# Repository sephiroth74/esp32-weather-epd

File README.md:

> **Fork Notice**: This is a fork of [lmarzen/esp32-weather-epd](https://github.com/lmarzen/esp32-weather-epd) with additional features:
> - **Multiple location support**: Cycle through different locations on each refresh

# ESP32 E-Paper Weather Display

A low-power weather display using a wifi-enabled ESP32 microcontroller and a 7.5" E-Paper display. Weather data is fetched from the OpenWeatherMap API, and an onboard sensor provides indoor temperature and humidity.

## Features

- Ultra-low power consumption: ~14μA in sleep, ~83mA during refresh (~15s).

- Long battery life: 6-12 months on a 5000mAh battery with 30-minute update frequency.

- Customizable display: Supports multiple languages, units, time/date formats, AQI scales, personalization options, and much more.

- Easy recharging: USB-C charging with battery monitoring.

The hourly outlook graph (bottom right) shows a line indicating temperature and shaded bars indicating probability of precipitation (or optionally volume of precipitation).

Here are two (slightly outdated) examples utilizing various configuration options:

## Contents

- [ESP32 E-Paper Weather Display](#esp32-e-paper-weather-display)
  - [Features](#features)
  - [Contents](#contents)
  - [Required Components](#required-components)
    - [Panel Support](#panel-support)
    - [Enclosure Options](#enclosure-options)
    - [Solder-Free Component Selection (Optional)](#solder-free-component-selection-optional)
  - [Setup Guide](#setup-guide)
    - [Wiring](#wiring)
    - [Configuration, Compilation, and Upload](#configuration-compilation-and-upload)
    - [OpenWeatherMap API Key](#openweathermap-api-key)
  - [Error Messages and Troubleshooting](#error-messages-and-troubleshooting)
    - [Low Battery](#low-battery)
    - [WiFi Connection](#wifi-connection)
    - [API Error](#api-error)
    - [Time Server Error](#time-server-error)
  - [Licensing](#licensing)

## Required Components

  Some links below are affiliate links. Using them helps support the project at no extra cost to you—thanks for your support!

  | Component Type  | Component                                    | Notes                                                     | Link                                                                         |
  |-----------------|----------------------------------------------|-----------------------------------------------------------|------------------------------------------------------------------------------|
  | ESP32           | FireBeetle 2 ESP32-E                         | Features low-power design, USB-C, and battery management. | Available [here](https://www.dfrobot.com/product-2195.html?tracking=PfSxQ8). |
  | E-Paper Display | See [Panel Support](#panel-support).         | See [Panel Support](#panel-support).                      | See [Panel Support](#panel-support).                                         |
  | Adapter Board   | DESPI-C02                                    | Waveshare HATs (rev 2.2/2.3) are not recommended.         | Available [here](https://www.aliexpress.us/item/3256804446769469.html).      |
  | Sensor          | BME280                                       | Temperature, humidity, and pressure. 3.3V/5V compatible.  | Available from multiple vendors.                                             |
  | Battery         | 3.7V LiPo w/ JST-PH2.0 connector             | Any capacity (e.g., 5000mAh for 6+ months runtime)        | Available from multiple vendors.                                             |
  | Enclosure       | See [Enclosure Options](#enclosure-options). | See [Enclosure Options](#enclosure-options).              | See [Enclosure Options](#enclosure-options).                                 |

Other items needed:
- Wires ("Jumper Wires" if looking to minimize/avoid soldering).
- Solder Iron + Solder (unless following [Solder-Free Component Selection](#solder-free-component-selection-optional)).
- Linux, Windows, or MacOS computer (used to configure and install ESP32 firmware).
- Push Button (optional, if you want a reset button mounted on your enslosure, else you can use the on-board reset button).

### Panel Support

  Waveshare and Good Display make equivalent panels. Either variant will work.

  | Panel                                   | Resolution | Colors          | Notes                                                                                                                 |
  |-----------------------------------------|------------|-----------------|-----------------------------------------------------------------------------------------------------------------------|
  | Waveshare 7.5in e-paper (v2)            | 800x480px  | Black/White     | Available [here](https://www.waveshare.com/product/7.5inch-e-paper.htm). (recommended)                                |
  | Good Display 7.5in e-paper (GDEY075T7)  | 800x480px  | Black/White     | [Temporarily Unavailable](https://www.aliexpress.com/item/3256802683908868.html)? (wrong product listed?)             |
  | Waveshare 7.5in e-Paper (B)             | 800x480px  | Red/Black/White | Available [here](https://www.waveshare.com/product/7.5inch-e-paper-b.htm).                                            |
  | Good Display 7.5in e-paper (GDEY075Z08) | 800x480px  | Red/Black/White | Available [here](https://www.aliexpress.com/item/3256803540460035.html).                                              |
  | Waveshare 7.3in ACeP e-Paper (F)        | 800x480px  | 7-Color         | Available [here](https://www.waveshare.com/product/displays/e-paper/epaper-1/7.3inch-e-paper-f.htm).                  |
  | Good Display 7.3in e-paper (GDEY073D46) | 800x480px  | 7-Color         | Available [here](https://www.aliexpress.com/item/3256805485098421.html).                                              |
  | Waveshare 7.5in e-paper (v1)            | 640x384px  | Black/White     | Limited support. Some information not displayed, see [image](showcase/demo-waveshare75-version1.jpg).                 |
  | Good Display 7.5in e-paper (GDEW075T8)  | 640x384px  | Black/White     | Limited support. Some information not displayed, see [image](showcase/demo-waveshare75-version1.jpg).                 |

  This software has limited support for accent colors. E-paper panels with additional colors tend to have longer refresh times, which will reduce battery life.

### Enclosure Options

You'll want a nice way to show off your project. Here are a few popular choices.

- DIY Wooden
  - I made a small stand by hollowing out a piece of wood from the bottom. On the back, I used a short USB extension cable so that I can charge the battery without needing to remove the components from the stand. I also wired a small reset button to refresh the display manually. Additionally, I 3d printed a cover for the bottom, which is held on by magnets. The E-paper screen is very thin, so I used a thin piece of acrylic to support it.
  - Measurements:
    - depth = 63mm <br>
      height = 49mm <br>
      width = 170.2mm (= width of the screen) <br>
      screen angle = 80deg <br>
      screen is 15mm from the front
- 3D Printable
  - Here is a list of community designs.
  
    | Contributor                                                          | Link                                                                                                     |
    |----------------------------------------------------------------------|----------------------------------------------------------------------------------------------------------|
    | [Kingfisher](https://www.printables.com/@Kingfisher_32821)           | [Printables](https://www.printables.com/model/1139047-weather-station-e-ink-frame)                       |
    | [Francois Allard](https://www.printables.com/@FrAllard_1585397)      | [Printables](https://www.printables.com/model/791477-weather-station-using-a-esp32)                      |
    | [3D Nate](https://www.printables.com/@3DNate_451157)                 | [Printables](https://www.printables.com/model/661183-e-ink-weather-station-frame)                        |
    | [Sven F.](https://github.com/Spanholz)                               | [Printables](https://www.printables.com/model/657756-case-for-esp32-weather-station)                     |
    | [Layers Studio](https://www.printables.com/@LayersStudio)            | [Printables](https://www.printables.com/model/655768-esp32-e-paper-weather-display-stand)                |
    | [PJ Veltri](https://www.printables.com/@PJVeltri_1590999)            | [Printables](https://www.printables.com/model/692944-base-and-display-holder-for-esp-32-e-paper-weather) |
    | [TheMeanCanEHdian](https://www.printables.com/@TheMeanCanEH_1207348) | [Printables](https://www.printables.com/model/841458-weather-display-enclosure)                          |
    | [MPHarms](https://www.thingiverse.com/mpharms/designs)               | [Thingiverse](https://www.thingiverse.com/thing:6666148)                                                 |
    | [Plaste-Metz](https://www.printables.com/@PlasteMetz_576567)         | [Printables](https://www.printables.com/model/1160924-weather-station-case)                              |

  - If you want to share your own 3D printable designs, your contributions are highly encouraged and welcome!
- Picture Frame

### Solder-Free Component Selection (Optional)

This project can be completed without any soldering, if you choose your component selection carefully.
- Buy "Jumper Wires" to connect your components.
- Buy the [FireBeetle 2 ESP32-E w/ Headers](https://www.dfrobot.com/product-2231.html?tracking=PfSxQ8).
- Buy a BME280 with headers soldered from the factory.
- Buy a reset switch that is compatible with jumper wires.

## Setup Guide

### Wiring

The battery can be charged by plugging the FireBeetle ESP32 into the wall via the USB-C connector while the battery is plugged into the ESP32's JST connector.

  > **Warning**
  > The polarity of JST-PH2.0 connectors is not standardized! You may need to swap the order of the wires in the connector.

NOTE: Waveshare now ships revision 2.3 of their e-paper HAT (no longer rev 2.2 ). Rev 2.3 has an additional `PWR` pin (not depicted in the wiring diagrams below); connect this pin to 3.3V.

IMPORTANT: The DESPI-C02 adapter has one physical switch that MUST be set correctly for the display to work.

- RESE: Set switch to position 0.47.

IMPORTANT: The Waveshare E-Paper Driver HAT has two physical switches that MUST be set correctly for the display to work.

- Display Config: Set switch to position B.

- Interface Config: Set switch to position 0.

Cut the low power pad for even longer battery life.

- From <https://wiki.dfrobot.com/FireBeetle_Board_ESP32_E_SKU_DFR0654>

  > Low Power Pad: This pad is specially designed for low power consumption. It is connected by default. You can cut off the thin wire in the middle with a knife to disconnect it. After disconnection, the static power consumption can be reduced by 500 μA. The power consumption can be reduced to 13 μA after controlling the maincontroller enter the sleep mode through the program. Note: when the pad is disconnected, you can only drive RGB LED light via the USB Power supply.

### Configuration, Compilation, and Upload

PlatformIO for VSCode is used for managing dependencies, code compilation, and uploading to ESP32.

1. Clone this repository or download and extract the .zip.

2. Install VSCode.

3. Follow these instructions to install the PlatformIO extension for VSCode: <https://platformio.org/install/ide?install=vscode>

4. Open the project in VSCode.

   a. File > Open Folder...

   b. Navigate to this project and select the folder called "platformio".

5. Configure Options.

   - Most configuration options are located in [config.cpp](platformio/src/config.cpp), with a few  in [config.h](platformio/include/config.h).

   - Important settings to configure in config.cpp:

     - WiFi credentials (ssid, password).

     - Open Weather Map API key (it's free, see next section for important notes about obtaining an API key).

     - Latitude and longitude.

     - Time and date formats.

     - Sleep duration.

   - Important settings to configure in config.h:

     - Units (Metric or Imperial).

   - Comments explain each option in detail.

6. Build and Upload Code.

   a. Connect ESP32 to your computer via USB.

   b. Click the upload arrow along the bottom of the VSCode window. (Should say "PlatformIO: Upload" if you hover over it.)

      - PlatformIO will automatically download the required third-party libraries, compile, and upload the code. :)

      - You will only see this if you have the PlatformIO extension installed.

      - If using a FireBeetle 2 ESP32-E and you receive the error `Wrong boot mode detected (0x13)! The chip needs to be in download mode.` unplug the power from the board, connect GPIO0 ([labeled 0/D5](https://wiki.dfrobot.com/FireBeetle_Board_ESP32_E_SKU_DFR0654#target_5)) to GND, and power it back up to put the board in download mode.

      - If you are getting other errors during the upload process, you may need to install drivers to allow you to upload code to the ESP32.

### OpenWeatherMap API Key

Sign up here to get an API key; it's free. <https://openweathermap.org/api>

This project will make calls to 2 different APIs ("One Call" and "Air Pollution").

- The One Call API 3.0 is only included in the "One Call by Call" subscription. This separate subscription includes 1,000 calls/day for free and allows you to pay only for the number of API calls made to this product.

Here's how to subscribe and avoid any credit card changes:
   - Go to <https://home.openweathermap.org/subscriptions/billing_info/onecall_30/base?key=base&service=onecall_30>
   - Follow the instructions to complete the subscription.
   - Go to <https://home.openweathermap.org/subscriptions> and set the "Calls per day (no more than)" to 1,000. This ensures you will never overrun the free calls.

## Error Messages and Troubleshooting

### Low Battery

This error screen appears once the battery voltage has fallen below LOW_BATTERY_VOLTAGE (default = 3.20v). The display will not refresh again until it detects battery voltage above LOW_BATTERY_VOLTAGE. When battery voltage is between LOW_BATTERY_VOLTAGE and VERY_LOW_BATTERY_VOLTAGE (default = 3.10v) the esp32 will deep-sleep for periods of LOW_BATTERY_SLEEP_INTERVAL (default = 30min) before checking battery voltage again. If the battery voltage falls between LOW_BATTERY_SLEEP_INTERVAL and CRIT_LOW_BATTERY_VOLTAGE (default = 3.00v), then the display will deep-sleep for periods VERY_LOW_BATTERY_SLEEP_INTERVAL (default = 120min). If battery voltage falls below CRIT_LOW_BATTERY_VOLTAGE, then the esp32 will enter hibernate mode and will require a manual push of the reset (RST) button to begin updating again.

<br clear="left"/>

### WiFi Connection

This error screen appears when the ESP32 fails to connect to WiFi. If the message reads "WiFi Connection Failed" this might indicate an incorrect password. If the message reads "SSID Not Available" this might indicate that you mistyped the SSID or that the esp32 is out of the range of the access point. The esp32 will retry once every SLEEP_DURATION (default = 30min).

<br clear="left"/>

### API Error

This error screen appears if an error (client or server) occurs when making an API request to OpenWeatherMap. The second line will give the error code followed by a descriptor phrase. Positive error codes correspond to HTTP response status codes, while error codes <= 0 indicate a client(esp32) error. The esp32 will retry once every SLEEP_DURATION (default = 30min).
<br/><br/>
In the example shown to the left, "401: Unauthorized" may be the result of an incorrect API key or that you are attempting to use the One Call v3 API without the proper account setup.

<br clear="left"/>

### Time Server Error

This error screen appears when the esp32 fails to fetch the time from NTP_SERVER_1/NTP_SERVER_2. This error sometimes occurs immediately after uploading to the esp32; in this case, just hit the reset button or wait for SLEEP_DURATION (default = 30min) and the esp32 to automatically retry. If the error persists, try selecting closer/lower latency time servers or increasing NTP_TIMEOUT.

<br clear="left"/>

## Licensing

esp32-weather-epd is licensed under the [GNU General Public License v3.0](LICENSE) with tools, fonts, and icons whose licenses are as follows:

| Name | License | Description |
|---------------------------------------------------------------------------------------------------------------|---------------------------------------------------------------------------------------|------------------------------------------------------------------------------------|
| [Adafruit-GFX-Library: fontconvert](https://github.com/adafruit/Adafruit-GFX-Library/tree/master/fontconvert) | [BSD License](fonts/fontconvert/license.txt) | CLI tool for preprocessing fonts to be used with the Adafruit_GFX Arduino library. |
| [pollutant-concentration-to-aqi](https://github.com/lmarzen/pollutant-concentration-to-aqi) | [GNU Lesser General Public License v2.1](platformio/lib/pollutant-concentration-to-aqi/LICENSE) | C library that converts pollutant concentrations to Air Quality Index(AQI). |
| [GNU FreeFont](https://www.gnu.org/software/freefont/) | [GNU General Public License v3.0](https://www.gnu.org/software/freefont/license.html) | Font Family |
| [Lato](https://fonts.google.com/specimen/Lato) | [SIL OFL v1.1](http://scripts.sil.org/OFL) | Font Family |
| [Montserrat](https://fonts.google.com/specimen/Montserrat) | [SIL OFL v1.1](http://scripts.sil.org/OFL) | Font Family |
| [Open Sans](https://fonts.google.com/specimen/Open+Sans) | [SIL OFL v1.1](http://scripts.sil.org/OFL) | Font Family |
| [Poppins](https://fonts.google.com/specimen/Poppins) | [SIL OFL v1.1](http://scripts.sil.org/OFL) | Font Family |
| [Quicksand](https://fonts.google.com/specimen/Quicksand) | [SIL OFL v1.1](http://scripts.sil.org/OFL) | Font Family |
| [Raleway](https://fonts.google.com/specimen/Raleway) | [SIL OFL v1.1](http://scripts.sil.org/OFL) | Font Family |
| [Roboto](https://fonts.google.com/specimen/Roboto) | [Apache License v2.0](https://www.apache.org/licenses/LICENSE-2.0) | Font Family |
| [Roboto Mono](https://fonts.google.com/specimen/Roboto+Mono) | [Apache License v2.0](https://www.apache.org/licenses/LICENSE-2.0) | Font Family |
| [Roboto Slab](https://fonts.google.com/specimen/Roboto+Slab) | [Apache License v2.0](https://www.apache.org/licenses/LICENSE-2.0) | Font Family |
| [Ubuntu font](https://design.ubuntu.com/font) | [Ubuntu Font Licence v1.0](https://ubuntu.com/legal/font-licence) | Font Family |
| [Weather Themed Icons](https://github.com/erikflowers/weather-icons) | [SIL OFL v1.1](http://scripts.sil.org/OFL) | (wi-**.svg) Weather icon family by Lukas Bischoff/Erik Flowers. |
| [Google Icons](https://fonts.google.com/icons) | [Apache License v2.0](https://www.apache.org/licenses/LICENSE-2.0) | (battery**.svg, visibility_icon.svg) Battery and visibility icons from Google Icons. |
| [Biological Hazard Symbol](https://svgsilh.com/image/37775.html) | [CC0 v1.0](https://en.wikipedia.org/wiki/Public_domain) | (biological_hazard_symbol.svg) Biohazard icon. |
| [House Icon](https://seekicon.com/free-icon/house_16) | [MIT License](http://opensource.org/licenses/mit-license.html) | (house.svg) House icon. |
| [Indoor Temerature/Humidity Icons](icons/svg) | [SIL OFL v1.1](http://scripts.sil.org/OFL) | (house_**.svg) Indoor temerature/humidity icons. |
| [Ionizing Radiation Symbol](https://svgsilh.com/image/309911.html) | [CC0 v1.0](https://creativecommons.org/publicdomain/zero/1.0/) | (ionizing_radiation_symbol.svg) Ionizing radiation icons. |
| [Phosphor Icons](https://github.com/phosphor-icons/homepage) | [MIT License](http://opensource.org/licenses/mit-license.html) | (wifi**.svg, warning_icon.svg, error_icon.svg) WiFi, Warning, and Error icons from Phosphor Icons. |
| [Wind Direction Icon](https://www.onlinewebfonts.com/icon/251550) | [CC BY v3.0](http://creativecommons.org/licenses/by/3.0) | (meteorological_wind_direction_**deg.svg) Meteorological wind direction icon from Online Web Fonts. |

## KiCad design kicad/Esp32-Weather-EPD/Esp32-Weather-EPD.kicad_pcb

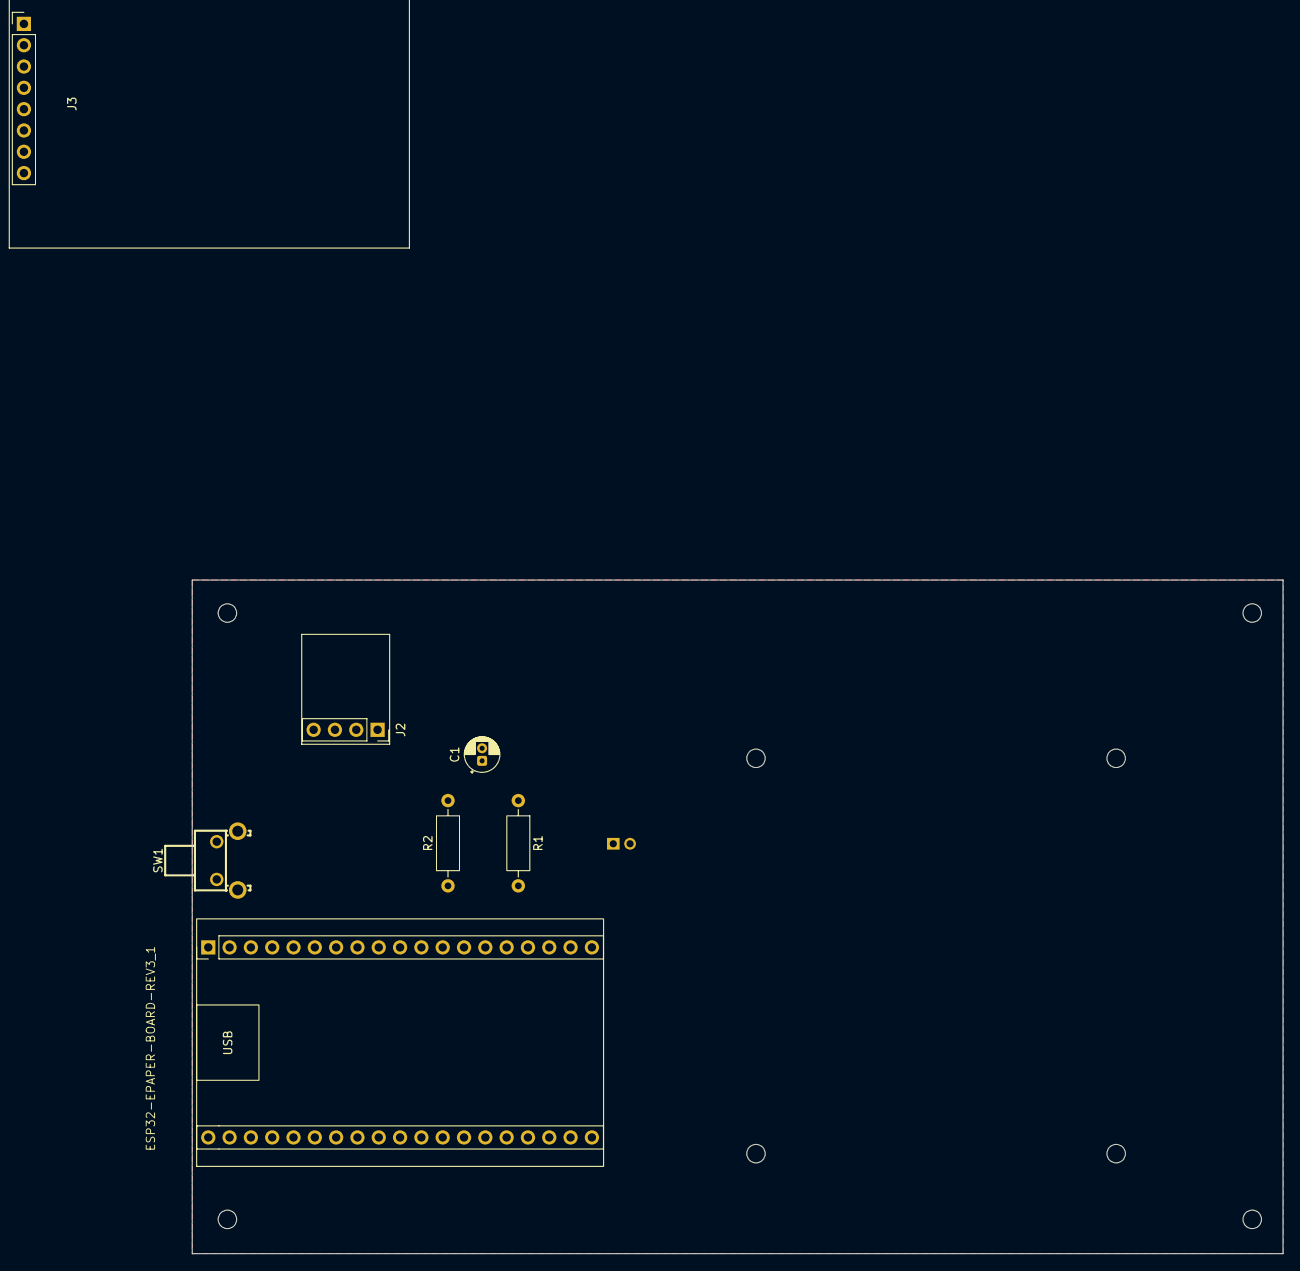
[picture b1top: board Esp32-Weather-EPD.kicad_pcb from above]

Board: 2 copper layers, 130.0 x 80.3 mm, 8 parts (1 on the bottom side), 14 nets, no tracks yet.

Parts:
C1: 1uF_50V; CP_Radial_D4.0mm_P1.50mm
ESP32-EPAPER-BOARD-REV3_1: Waveshare E-Paper Driver Board Rev.3 - ESP32
J2: PINHD_1x4_Female; PinSocket_1x04_P2.54mm_Vertical
J3: PINHD_1x8_Male; PinHeader_1x08_P2.54mm_Vertical
R1: 330k; R_Axial_DIN0207_L6.3mm_D2.5mm_P10.16mm_Horizontal
R2: 180k; R_Axial_DIN0207_L6.3mm_D2.5mm_P10.16mm_Horizontal
SW1: SW-TH_1-1825027-4
U2: CONN-TH_S2B-PH-K-S-LF-SN

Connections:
+4V: ESP32-EPAPER-BOARD-REV3_1.5V, R1.1, U2.1
/3v3: ESP32-EPAPER-BOARD-REV3_1.3V3, J2.4, J3.8
/BSY: ESP32-EPAPER-BOARD-REV3_1.P25 (P25/BUSY), J3.1
/CS: ESP32-EPAPER-BOARD-REV3_1.P15 (P15/CS), J3.4
/DC: ESP32-EPAPER-BOARD-REV3_1.P27 (P27/DC), J3.3
/GND2: ESP32-EPAPER-BOARD-REV3_1.GND, J2.3, J3.7, SW1.1
/RST: ESP32-EPAPER-BOARD-REV3_1.P26 (P26/RST), J3.2
/SCK: ESP32-EPAPER-BOARD-REV3_1.P13 (P13/SCK), J3.5
/SCL: ESP32-EPAPER-BOARD-REV3_1.P23, J2.2
/SDA: ESP32-EPAPER-BOARD-REV3_1.P22, J2.1
/SDI: ESP32-EPAPER-BOARD-REV3_1.P14 (P14/DIN), J3.6
GND1: C1.2, R2.2, U2.2
unnamed: C1.1, ESP32-EPAPER-BOARD-REV3_1.P4, R1.2, R2.1
unnamed: ESP32-EPAPER-BOARD-REV3_1.EN (~EN), SW1.2

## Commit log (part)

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2024-12-18 espressif32
2024-12-19 added location cycle
2024-12-19 removed and deleted api key
2024-12-19 restored bme 280 support
2025-04-14 36 hours + using local config file
2025-04-23 font
2025-04-26 config
2025-05-11 added schematic
    using resistors to calculate battery voltage
2025-06-21 battery reader
2025-06-22 comments
2025-07-03 dont kill if air pollution cannot be retrieved
2025-07-04 7 colors
2025-07-07 kicad
2025-07-14 added battery gauge support
2025-07-15 refactoring
2025-07-17 battery + using nano esp32
2025-08-08 arduino nano esp32 for 7 colors display in zurich
2025-08-15 moving configuration to platformio.ini
    added new board
2025-08-16 battery
2025-08-17 using external config
2025-08-17 external config
2025-08-26 new config
2025-11-17 toggle deep sleep
2025-11-17 merged with main
2025-11-17 removed unused constant
2025-11-17 builtin led on/off
2025-11-18 pulse led
2025-11-18 NUM_LOCATIONS exported
2025-11-19 removed static assert
2025-12-04 changes to compile for seed studio esp32 c6
2025-12-04 added display 6 and 7 colors
2025-12-04 using pioarduino platform for seed studio esp32 c6
2026-03-24 waveshare esp32 c6 zero
2026-03-24 merged
2026-03-24 display utils and locale
2026-03-24 still merging
